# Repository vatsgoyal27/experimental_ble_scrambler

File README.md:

# BLE Experimental FHSS Test Platform

An experimental multi-radio platform built around the **nRF24L01+** for investigating frequency hopping behavior across the 2.4 GHz ISM band.

> **Disclaimer**
>
> This project is intended solely for laboratory testing, RF characterization, and educational purposes inside controlled environments. It is **not** intended for interfering with wireless communications or transmitting on frequencies in violation of local regulations.

---

## Overview

This board contains:

- Raspberry Pi Pico W controller
- Three independent nRF24L01+ transceivers
- Three external RF power amplifiers
- Individual RF filtering stages
- SMA antenna connectors for each RF chain

The objective is to create a configurable RF test platform capable of:

- Continuous carrier generation
- Channel sweeping
- Experimental frequency hopping
- Timing analysis
- Multi-radio synchronization
- BLE advertising channel experiments

---

## Hardware

### Controller

- Raspberry Pi Pico W
- 3.3 V logic

### RF Chain (×3)

Each RF path contains:

```
Pico SPI
      │
      ▼
nRF24L01+
      │
      ▼
2.45 GHz RF Filter
      │
      ▼
RF2401C Power Amplifier
      │
      ▼
2450LP14A100T Matching Network
      │
      ▼
SMA Connector
```

Each radio has:

- Dedicated 16 MHz crystal
- Local decoupling
- Separate CE control
- Shared SPI bus
- Individual RF output chain

---

## Schematic

The design currently consists of three identical RF sections driven from a common SPI interface.

Features include:

- SPI shared between all radios
- Independent CE lines
- External RF front-end
- Matching network
- Filtered antenna output

---

## Current Firmware

Current firmware configures an nRF24L01+ as:

- Transmitter mode
- Auto ACK disabled
- CRC disabled
- 2 Mbps
- Maximum PA level
- Constant carrier enabled

Example initialization:

```cpp
radio.setAutoAck(false);
radio.stopListening();
radio.setRetries(0,0);
radio.setPayloadSize(5);
radio.setAddressWidth(3);
radio.setPALevel(RF24_PA_MAX);
radio.setDataRate(RF24_2MBPS);
radio.setCRCLength(RF24_CRC_DISABLED);

radio.startConstCarrier(RF24_PA_MAX, channel);
```

---

## Experimental Channel Sweep

The current proof-of-concept changes the RF channel by repeatedly calling

```cpp
radio.setChannel(channel);
```

Example sweep:

```cpp
for (int i = 0; i < 79; i++)
{
    radio.setChannel(i);
}
```

---

## BLE Advertising Channel Test

The firmware also demonstrates hopping across the three BLE advertising channels.

```cpp
byte ble_channels[] =
{
    37,
    38,
    39
};

for(int i=0;i<3;i++)
{
    radio.setChannel(ble_channels[i]);
}
```

This serves as a simple experiment in channel switching behavior rather than implementing the Bluetooth Low Energy protocol itself.

---

## Project Goals

- [x] Multi-radio PCB
- [x] External PA integration
- [x] RF filtering
- [x] Basic firmware
- [x] Constant carrier generation
- [x] Channel switching
- [ ] Precise timing control
- [ ] Simultaneous multi-radio hopping
- [ ] DMA-driven SPI control
- [ ] RP2040 PIO synchronization
- [ ] Measurement using SDR
- [ ] Spectrum characterization

---

## Requirements

### Hardware

- Raspberry Pi Pico W
- 3 × nRF24L01+
- RF2401C
- 2450LP14A1002T filter
- 3.3 V power supply
- Antennas or appropriate RF loads for testing

### Software

- Arduino IDE
- RF24 library
- Raspberry Pi Pico board package

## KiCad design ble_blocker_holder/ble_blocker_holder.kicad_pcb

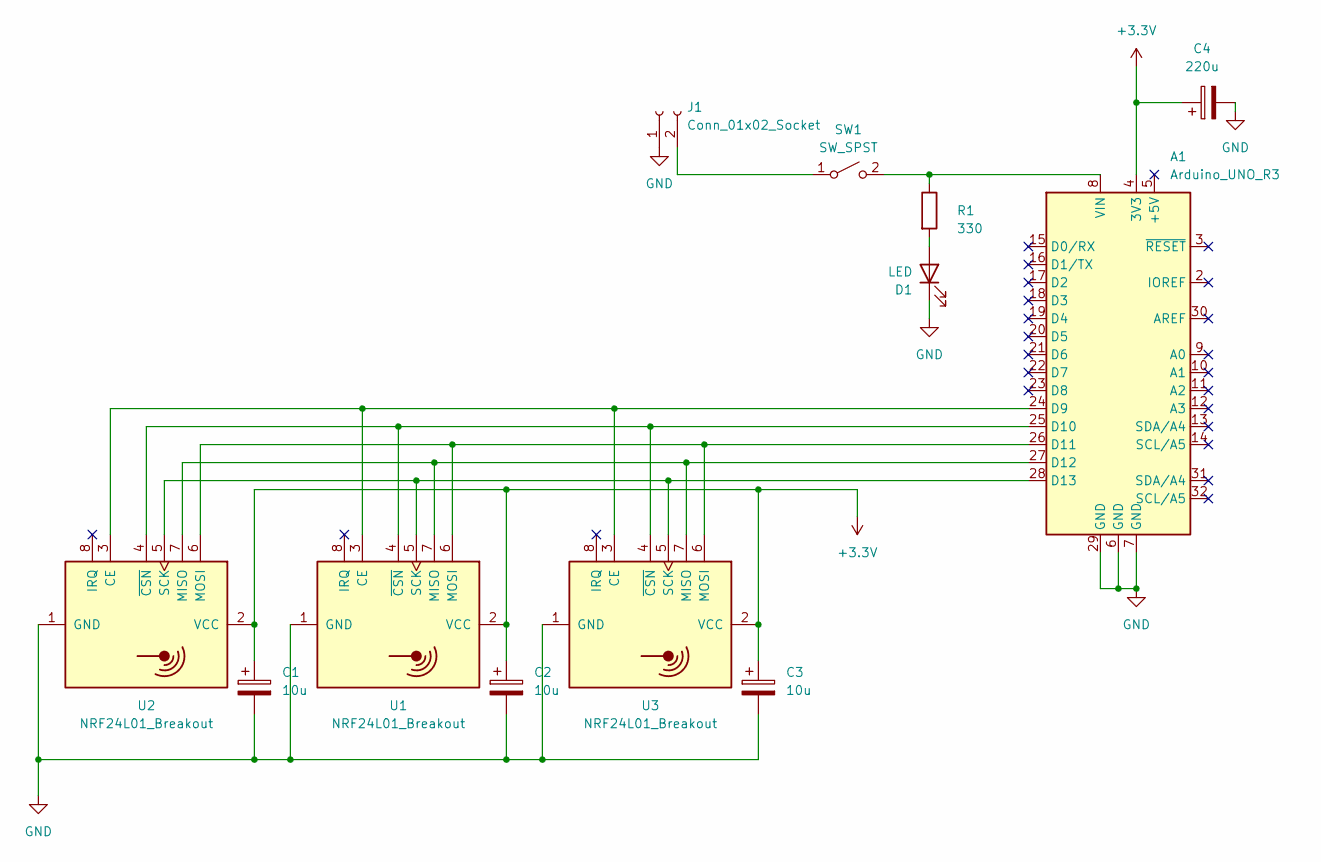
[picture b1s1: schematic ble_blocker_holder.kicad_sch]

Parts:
A1: Arduino_UNO_R3
C1, C2, C3: 10u; CP_Radial_D10.0mm_P2.50mm
C4: 220u; CP_Radial_D12.5mm_P5.00mm
D1: LED; LED_D5.0mm
J1: Conn_01x02_Socket; PinSocket_1x02_P2.54mm_Vertical
R1: 330; R_Axial_DIN0207_L6.3mm_D2.5mm_P7.62mm_Horizontal
SW1: SW_SPST; SW_DIP_SPSTx01_Slide_9.78x4.72mm_W7.62mm_P2.54mm
U1, U2, U3: NRF24L01_Breakout; nRF24L01_Breakout

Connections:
+3.3V: A1.4 (3V3), C1.1, C2.1, C3.1, C4.1, U1.2 (VCC), U2.2 (VCC), U3.2 (VCC)
GND: A1.6 (GND), A1.7 (GND), A1.29 (GND), C1.2, C2.2, C3.2, C4.2, D1.1 (K), J1.1, U1.1 (GND), U2.1 (GND), U3.1 (GND)
unnamed: A1.24 (D9), U1.3 (CE), U2.3 (CE), U3.3 (CE)
unnamed: A1.25 (D10), U1.4 (~CSN), U2.4 (~CSN), U3.4 (~CSN)
unnamed: A1.26 (D11), U1.6 (MOSI), U2.6 (MOSI), U3.6 (MOSI)
unnamed: A1.27 (D12), U1.7 (MISO), U2.7 (MISO), U3.7 (MISO)
unnamed: A1.28 (D13), U1.5 (SCK), U2.5 (SCK), U3.5 (SCK)
unnamed: A1.8 (VIN), R1.1, SW1.2 (B)
unnamed: D1.2 (A), R1.2
unnamed: J1.2, SW1.1 (A)

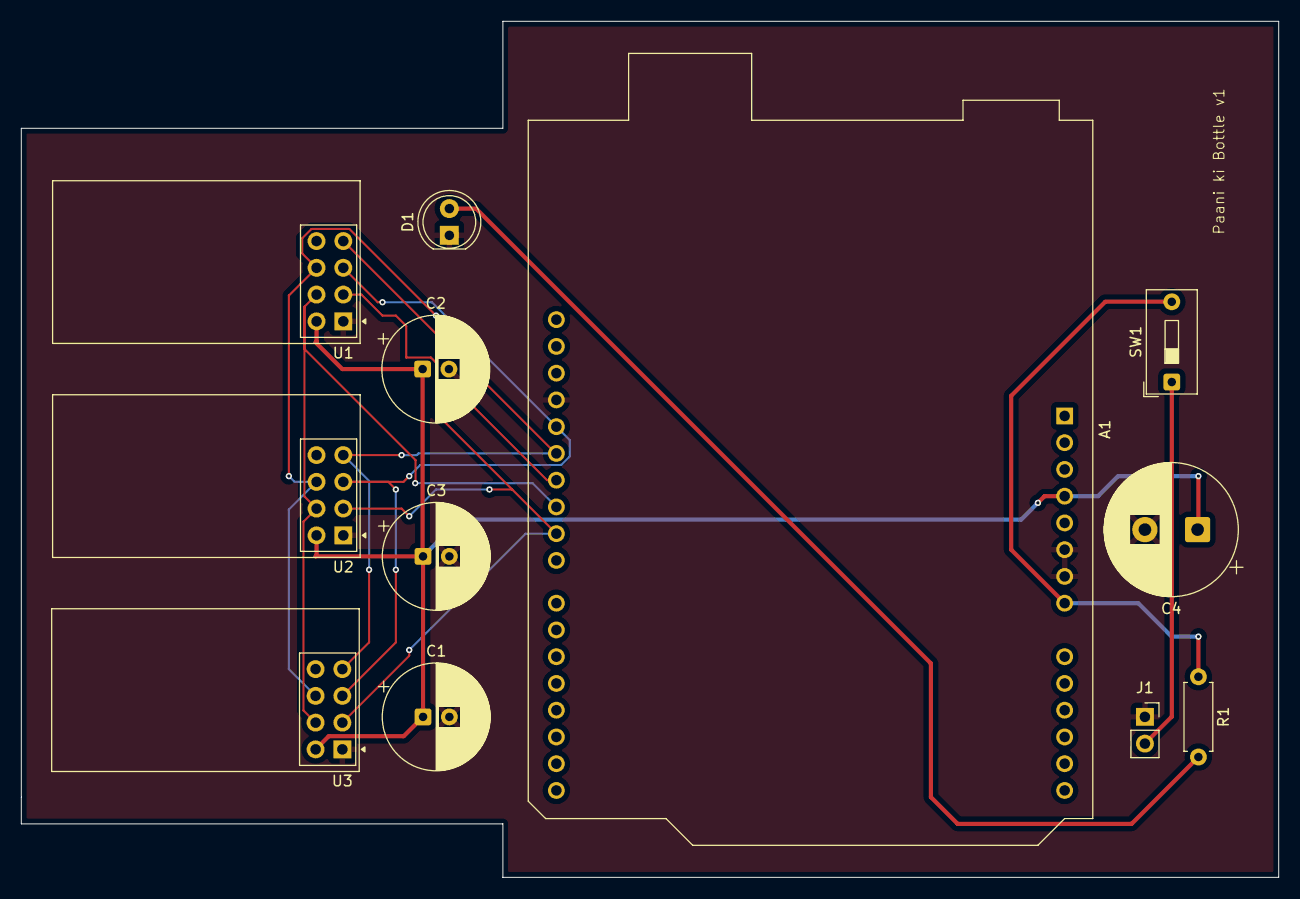
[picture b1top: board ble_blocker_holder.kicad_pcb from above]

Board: 2 copper layers, 119.4 x 81.3 mm, 12 parts (0 on the bottom side), 10 nets.

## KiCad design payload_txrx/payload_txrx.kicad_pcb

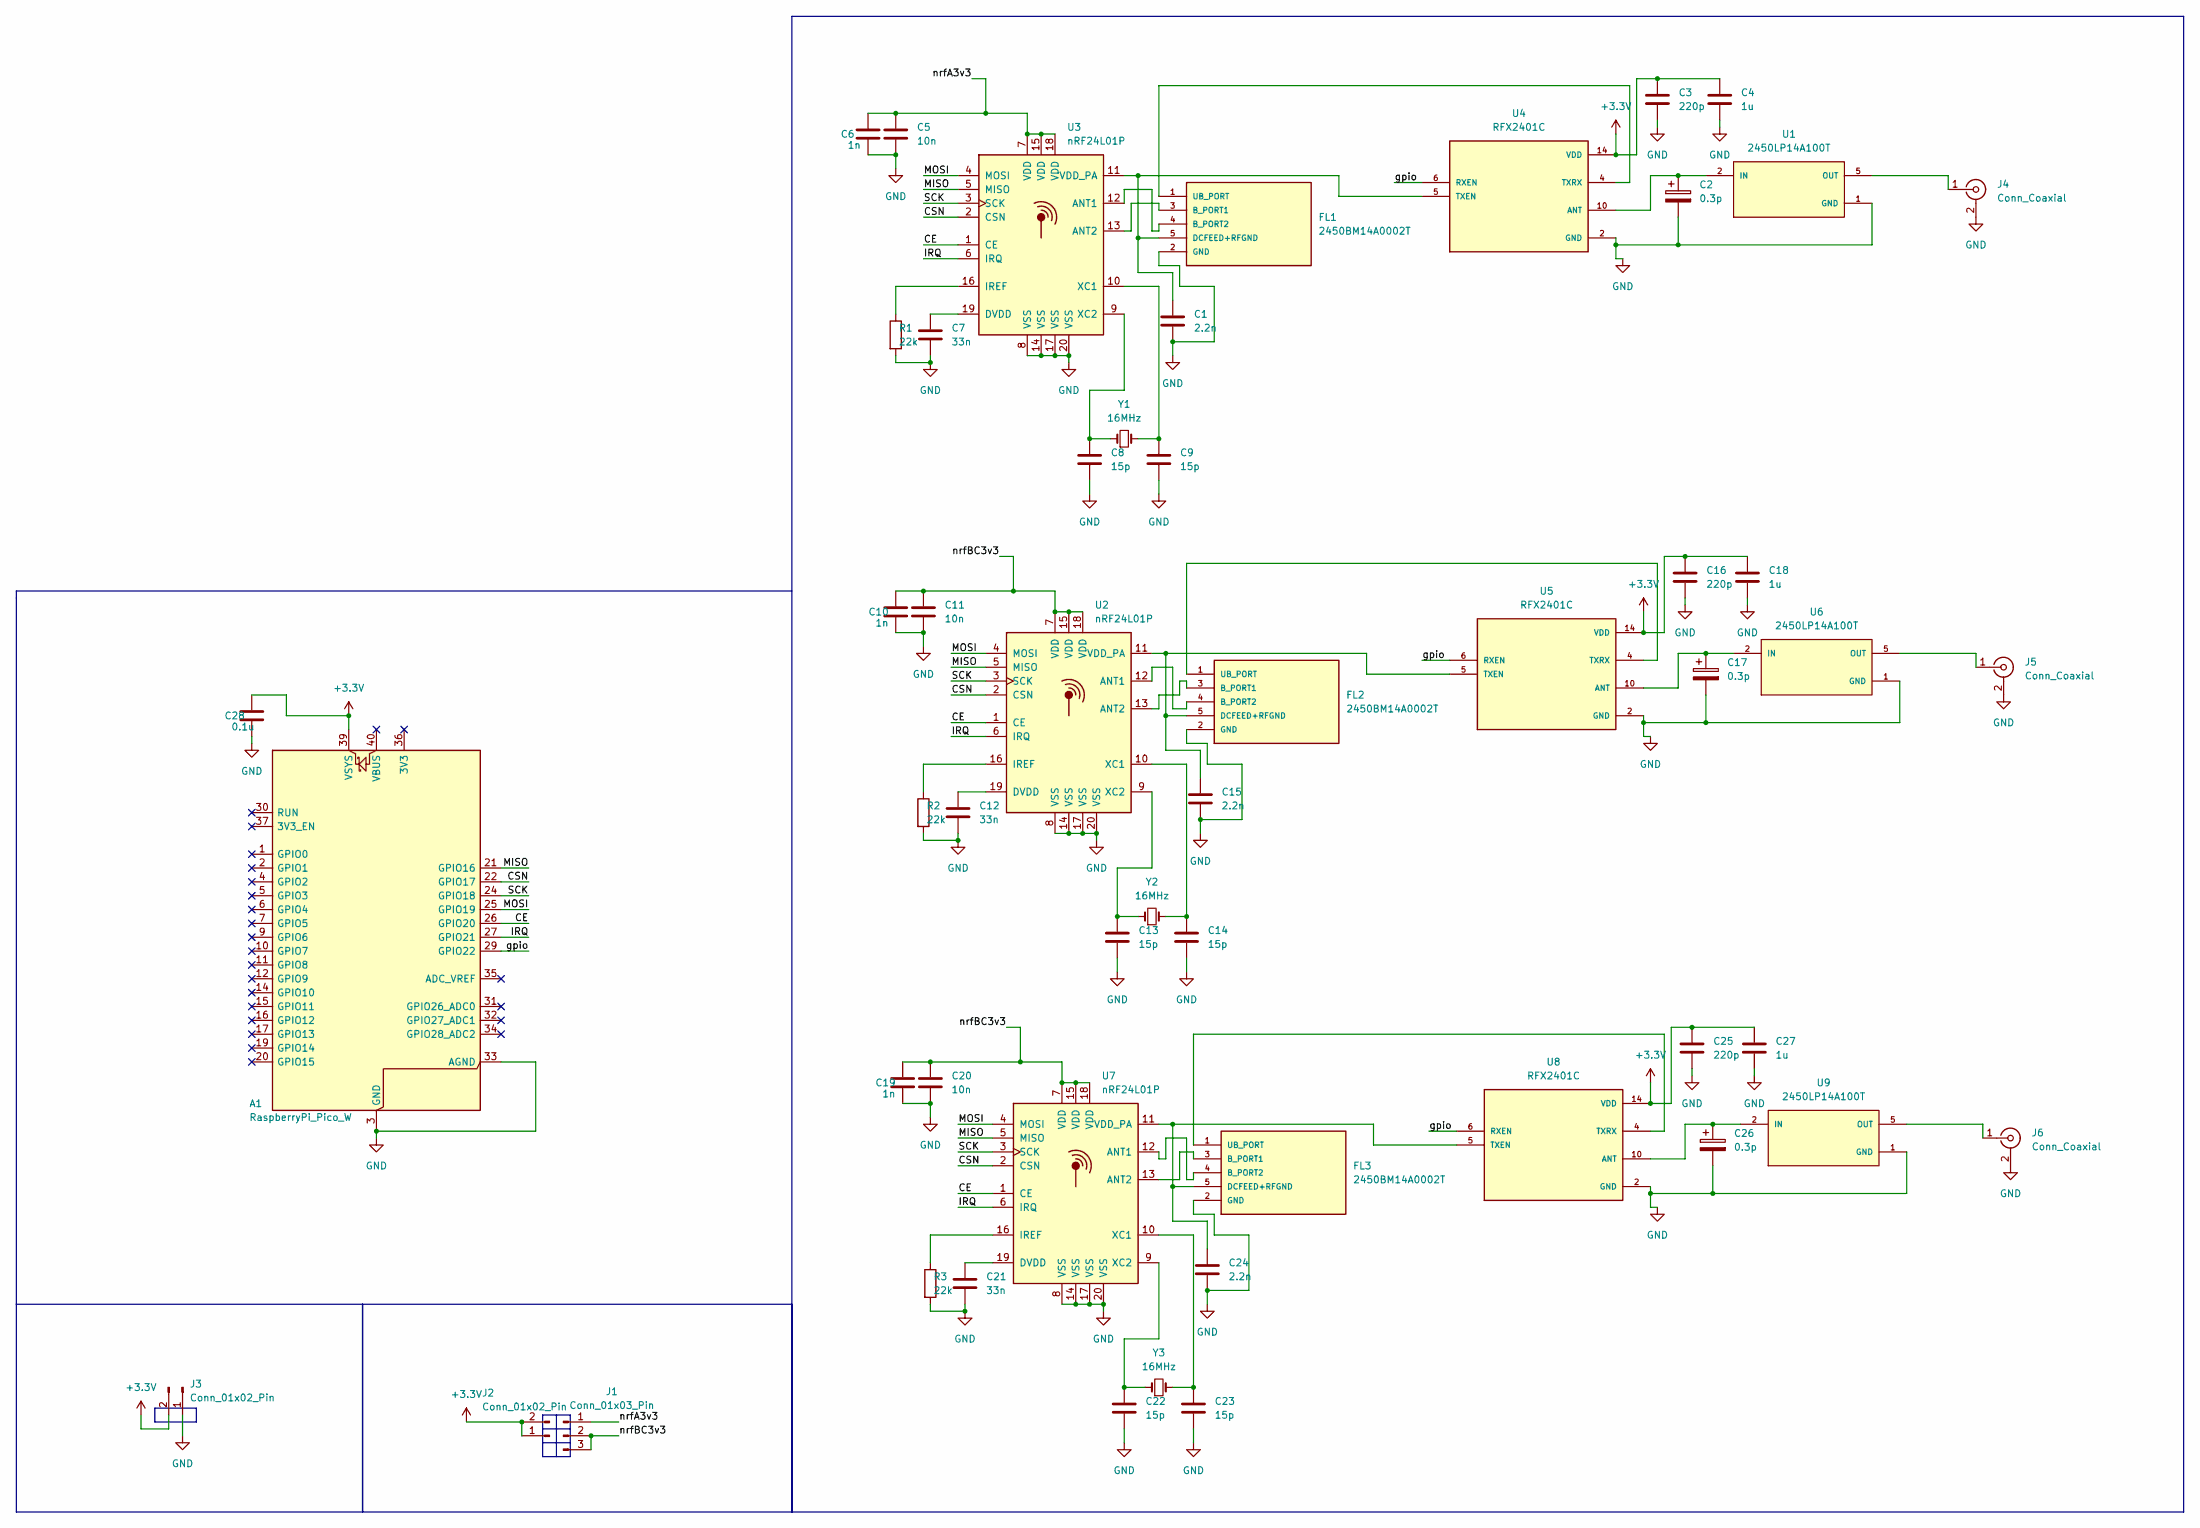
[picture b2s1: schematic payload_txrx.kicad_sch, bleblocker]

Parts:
A1: RaspberryPi_Pico_W; RaspberryPi_Pico_W_SMD_HandSolder
C1, C15, C24: 2.2n; C_0402_1005Metric
C2, C17, C26: 0.3p; C_0402_1005Metric
C3, C16, C25: 220p; C_0402_1005Metric
C4, C18, C27: 1u; C_0402_1005Metric
C5, C11, C20: 10n; C_0402_1005Metric
C6, C10, C19: 1n; C_0402_1005Metric
C7, C12, C21: 33n; C_0402_1005Metric
C8, C9, C13, C14, C22, C23: 15p; C_0402_1005Metric
C28: 0.1u; C_0402_1005Metric
FL1, FL2, FL3: 2450BM14A0002T; FIL_2450BM14A0002T
J1: Conn_01x03_Pin; PinHeader_1x03_P1.27mm_Vertical
J2, J3: Conn_01x02_Pin; PinHeader_1x02_P1.27mm_Vertical
J4, J5, J6: Conn_Coaxial; SMA_Molex_73251-2120_EdgeMount_Horizontal
R1, R2, R3: 22k; R_0402_1005Metric
U1, U6, U9: 2450LP14A100T; ICCAF50P160X80X70-6N; PARTREV 06/23/03
U2, U3, U7: nRF24L01P; QFN-20-1EP_4x4mm_P0.5mm_EP2.5x2.5mm
U4, U5, U8: RFX2401C; QFN50P300X300X60-17N
Y1, Y2, Y3: 16MHz; Crystal_SMD_3225-4Pin_3.2x2.5mm

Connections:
+3.3V: A1.39 (VSYS), C3.1, C4.1, C16.1, C18.1, C25.1, C27.1, C28.1, J2.1, J2.2, J3.2, U4.14 (VDD), U4.16 (VDD), U5.14 (VDD), U5.16 (VDD), U8.14 (VDD), U8.16 (VDD)
/CE: A1.26 (GPIO20), U2.1 (CE), U3.1 (CE), U7.1 (CE)
/CSN: A1.22 (GPIO17), U2.2 (CSN), U3.2 (CSN), U7.2 (CSN)
/IRQ: A1.27 (GPIO21), U2.6 (IRQ), U3.6 (IRQ), U7.6 (IRQ)
/MISO: A1.21 (GPIO16), U2.5 (MISO), U3.5 (MISO), U7.5 (MISO)
/MOSI: A1.25 (GPIO19), U2.4 (MOSI), U3.4 (MOSI), U7.4 (MOSI)
/SCK: A1.24 (GPIO18), U2.3 (SCK), U3.3 (SCK), U7.3 (SCK)
/gpio: A1.29 (GPIO22), U4.6 (RXEN), U5.6 (RXEN), U8.6 (RXEN)
/nrfA3v3: C5.1, C6.1, J1.1, U3.7 (VDD), U3.15 (VDD), U3.18 (VDD)
/nrfBC3v3: C10.1, C11.1, C19.1, C20.1, J1.2, J1.3, U2.7 (VDD), U2.15 (VDD), U2.18 (VDD), U7.7 (VDD), U7.15 (VDD), U7.18 (VDD)
GND: A1.3 (GND), A1.8 (GND), A1.13 (GND), A1.18 (GND), A1.23 (GND), A1.28 (GND), A1.33 (AGND), A1.38 (GND), C1.2, C2.2, C3.2, C4.2, C5.2, C6.2, C7.2, C8.2, C9.2, C10.2, C11.2, C12.2, C13.2, C14.2, C15.2, C16.2, C17.2, C18.2, C19.2, C20.2, C21.2, C22.2, C23.2, C24.2, C25.2, C26.2, C27.2, C28.2, FL1.2 (GND), FL2.2 (GND), FL3.2 (GND), J3.1, J4.2 (Ext), J5.2 (Ext), J6.2 (Ext), R1.2, R2.2, R3.2, U1.1 (GND), U1.3 (GND), U1.4 (GND), U1.6 (GND), U2.8 (VSS), U2.14 (VSS), U2.17 (VSS), U2.20 (VSS), U3.8 (VSS), U3.14 (VSS), U3.17 (VSS), U3.20 (VSS), U4.2 (GND), U4.3 (GND), U4.8 (GND), U4.9 (GND), U4.11 (GND), U4.17 (GND), U5.2 (GND), U5.3 (GND), U5.8 (GND), U5.9 (GND), U5.11 (GND), U5.17 (GND), U6.1 (GND), U6.3 (GND), U6.4 (GND), U6.6 (GND), U7.8 (VSS), U7.14 (VSS), U7.17 (VSS), U7.20 (VSS), U8.2 (GND), U8.3 (GND), U8.8 (GND), U8.9 (GND), U8.11 (GND), U8.17 (GND), U9.1 (GND), U9.3 (GND), U9.4 (GND), U9.6 (GND)
unnamed: FL1.3 (B_PORT1), U3.13 (ANT2)
unnamed: FL1.4 (B_PORT2), U3.12 (ANT1)
unnamed: C1.1, FL1.5 (DCFEED+RFGND), U3.11 (VDD_PA), U4.5 (TXEN)
unnamed: FL1.1 (UB_PORT), U4.4 (TXRX)
unnamed: FL2.3 (B_PORT1), U2.13 (ANT2)
unnamed: FL2.4 (B_PORT2), U2.12 (ANT1)
unnamed: C15.1, FL2.5 (DCFEED+RFGND), U2.11 (VDD_PA), U5.5 (TXEN)
unnamed: FL2.1 (UB_PORT), U5.4 (TXRX)
unnamed: FL3.3 (B_PORT1), U7.13 (ANT2)
unnamed: FL3.4 (B_PORT2), U7.12 (ANT1)
unnamed: C24.1, FL3.5 (DCFEED+RFGND), U7.11 (VDD_PA), U8.5 (TXEN)
unnamed: FL3.1 (UB_PORT), U8.4 (TXRX)
unnamed: J4.1 (In), U1.5 (OUT)
unnamed: J5.1 (In), U6.5 (OUT)
unnamed: J6.1 (In), U9.5 (OUT)
unnamed: C2.1, U1.2 (IN), U4.10 (ANT)
unnamed: C12.1, U2.19 (DVDD)
unnamed: R2.1, U2.16 (IREF)
unnamed: C14.1, U2.10 (XC1), Y2.2
unnamed: C13.1, U2.9 (XC2), Y2.1
unnamed: C7.1, U3.19 (DVDD)
unnamed: R1.1, U3.16 (IREF)
unnamed: C9.1, U3.10 (XC1), Y1.2
unnamed: C8.1, U3.9 (XC2), Y1.1
unnamed: C17.1, U5.10 (ANT), U6.2 (IN)
unnamed: C21.1, U7.19 (DVDD)
unnamed: R3.1, U7.16 (IREF)
unnamed: C23.1, U7.10 (XC1), Y3.2
unnamed: C22.1, U7.9 (XC2), Y3.1
unnamed: C26.1, U8.10 (ANT), U9.2 (IN)

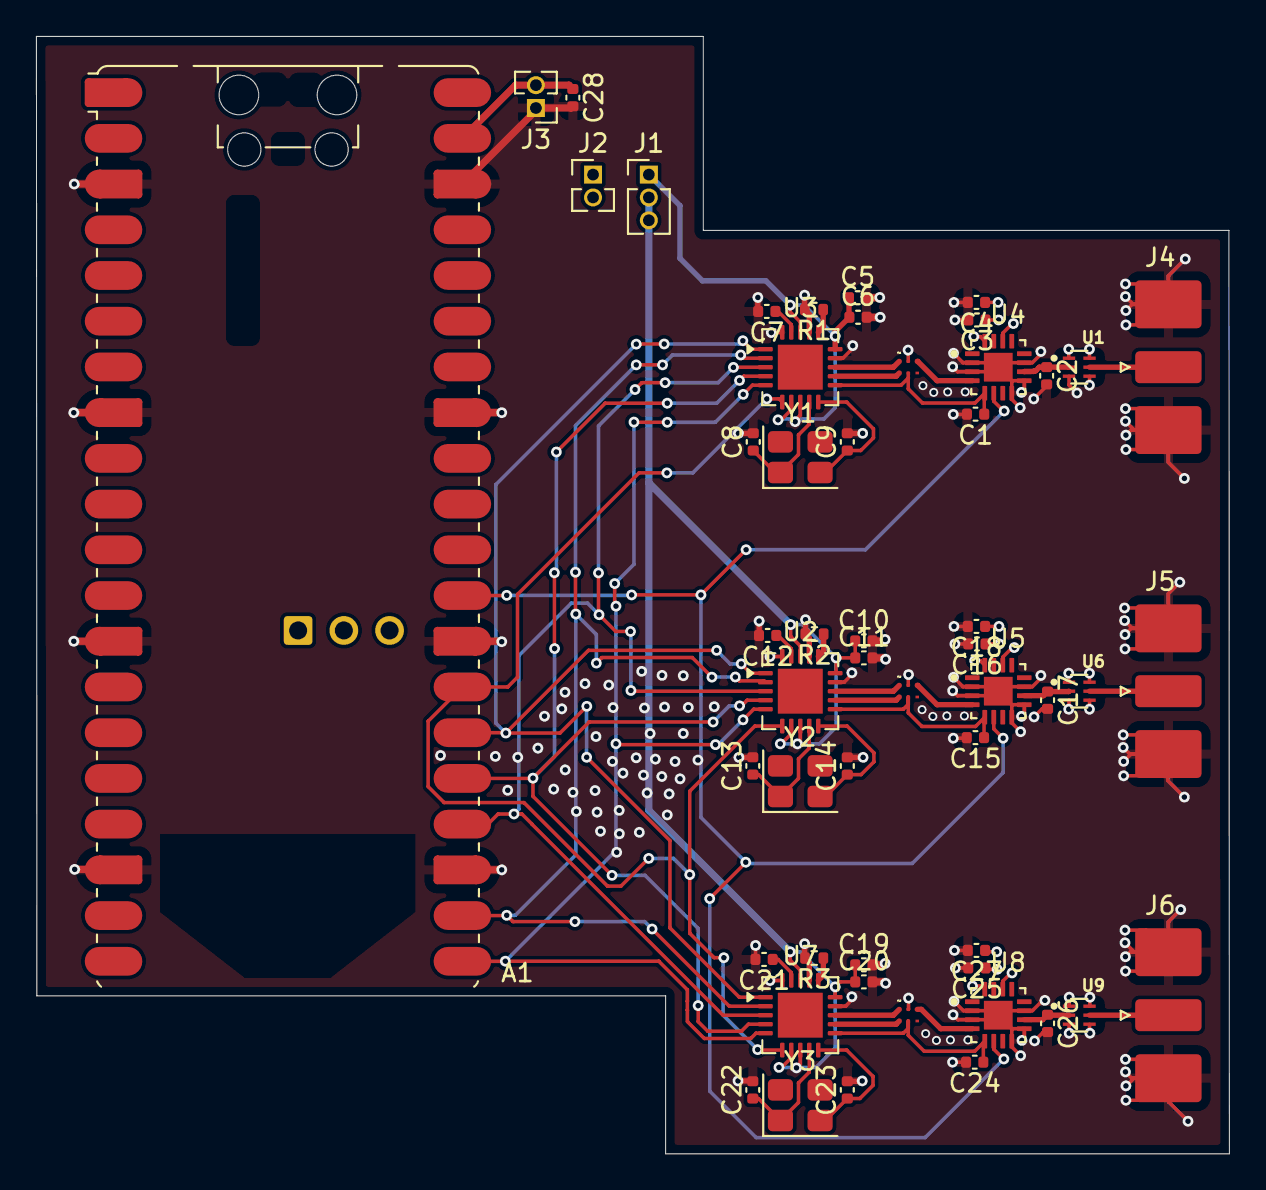
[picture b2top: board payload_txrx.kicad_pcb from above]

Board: 4 copper layers, 66.3 x 62.1 mm, 53 parts (0 on the bottom side), 41 nets.

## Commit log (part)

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2026-06-28 project items
    code is for arduino and the board is for pico, will adapt code for the pico soon
2026-06-28 original attempt
    an older pcb using aughter boards to save on rf planning
